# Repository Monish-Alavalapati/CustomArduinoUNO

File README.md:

# CustomArduinoUNO
Made a custom arduino PCB design which is cost effective and has optimized power management
## Overview

This repository contains the necessary files for the custom Arduino board designed using KiCad software. It includes the PCB design, Gerber files, and schematic layout.

## Files Included

1. **PCB Design File**: This file contains the design of the custom Arduino board. It's in KiCad format (.kicad_pcb) and can be opened using KiCad software for further modification.

2. **Gerber Files**: Gerber files are industry-standard files used for PCB manufacturing. These files contain all the necessary information for the fabrication of the PCB. They include layers such as copper traces, solder mask, and silkscreen.

3. **Schematic Layout**: The schematic layout of the custom Arduino board is provided in KiCad format (.sch). It shows the connections and components used in the design.

## How to Use

### Viewing the PCB Design and Schematic Layout

1. Install KiCad: If you haven't already, download and install KiCad from [KiCad's official website](https://www.kicad.org/).

2. Open Files:
   - To view the PCB design, open the `.kicad_pcb` file using KiCad's PCB Layout Editor.
   - To view the schematic layout, open the `.sch` file using KiCad's Schematic Editor.

### Manufacturing the PCB

1. Gerber Files: These are the files you'll need to submit to your PCB manufacturer. Most manufacturers have instructions on their websites for uploading Gerber files.

2. Verify Design: Before sending the files for manufacturing, double-check the design to ensure all connections and components are as intended.

3. Fabrication: Upload the Gerber files to your chosen PCB manufacturer and follow their instructions for fabrication. Make sure to specify any special requirements or preferences.

### Customization

Feel free to modify the design according to your requirements. You can use KiCad to make changes to the PCB layout or schematic as needed. Remember to update the Gerber files if significant changes are made before fabrication.

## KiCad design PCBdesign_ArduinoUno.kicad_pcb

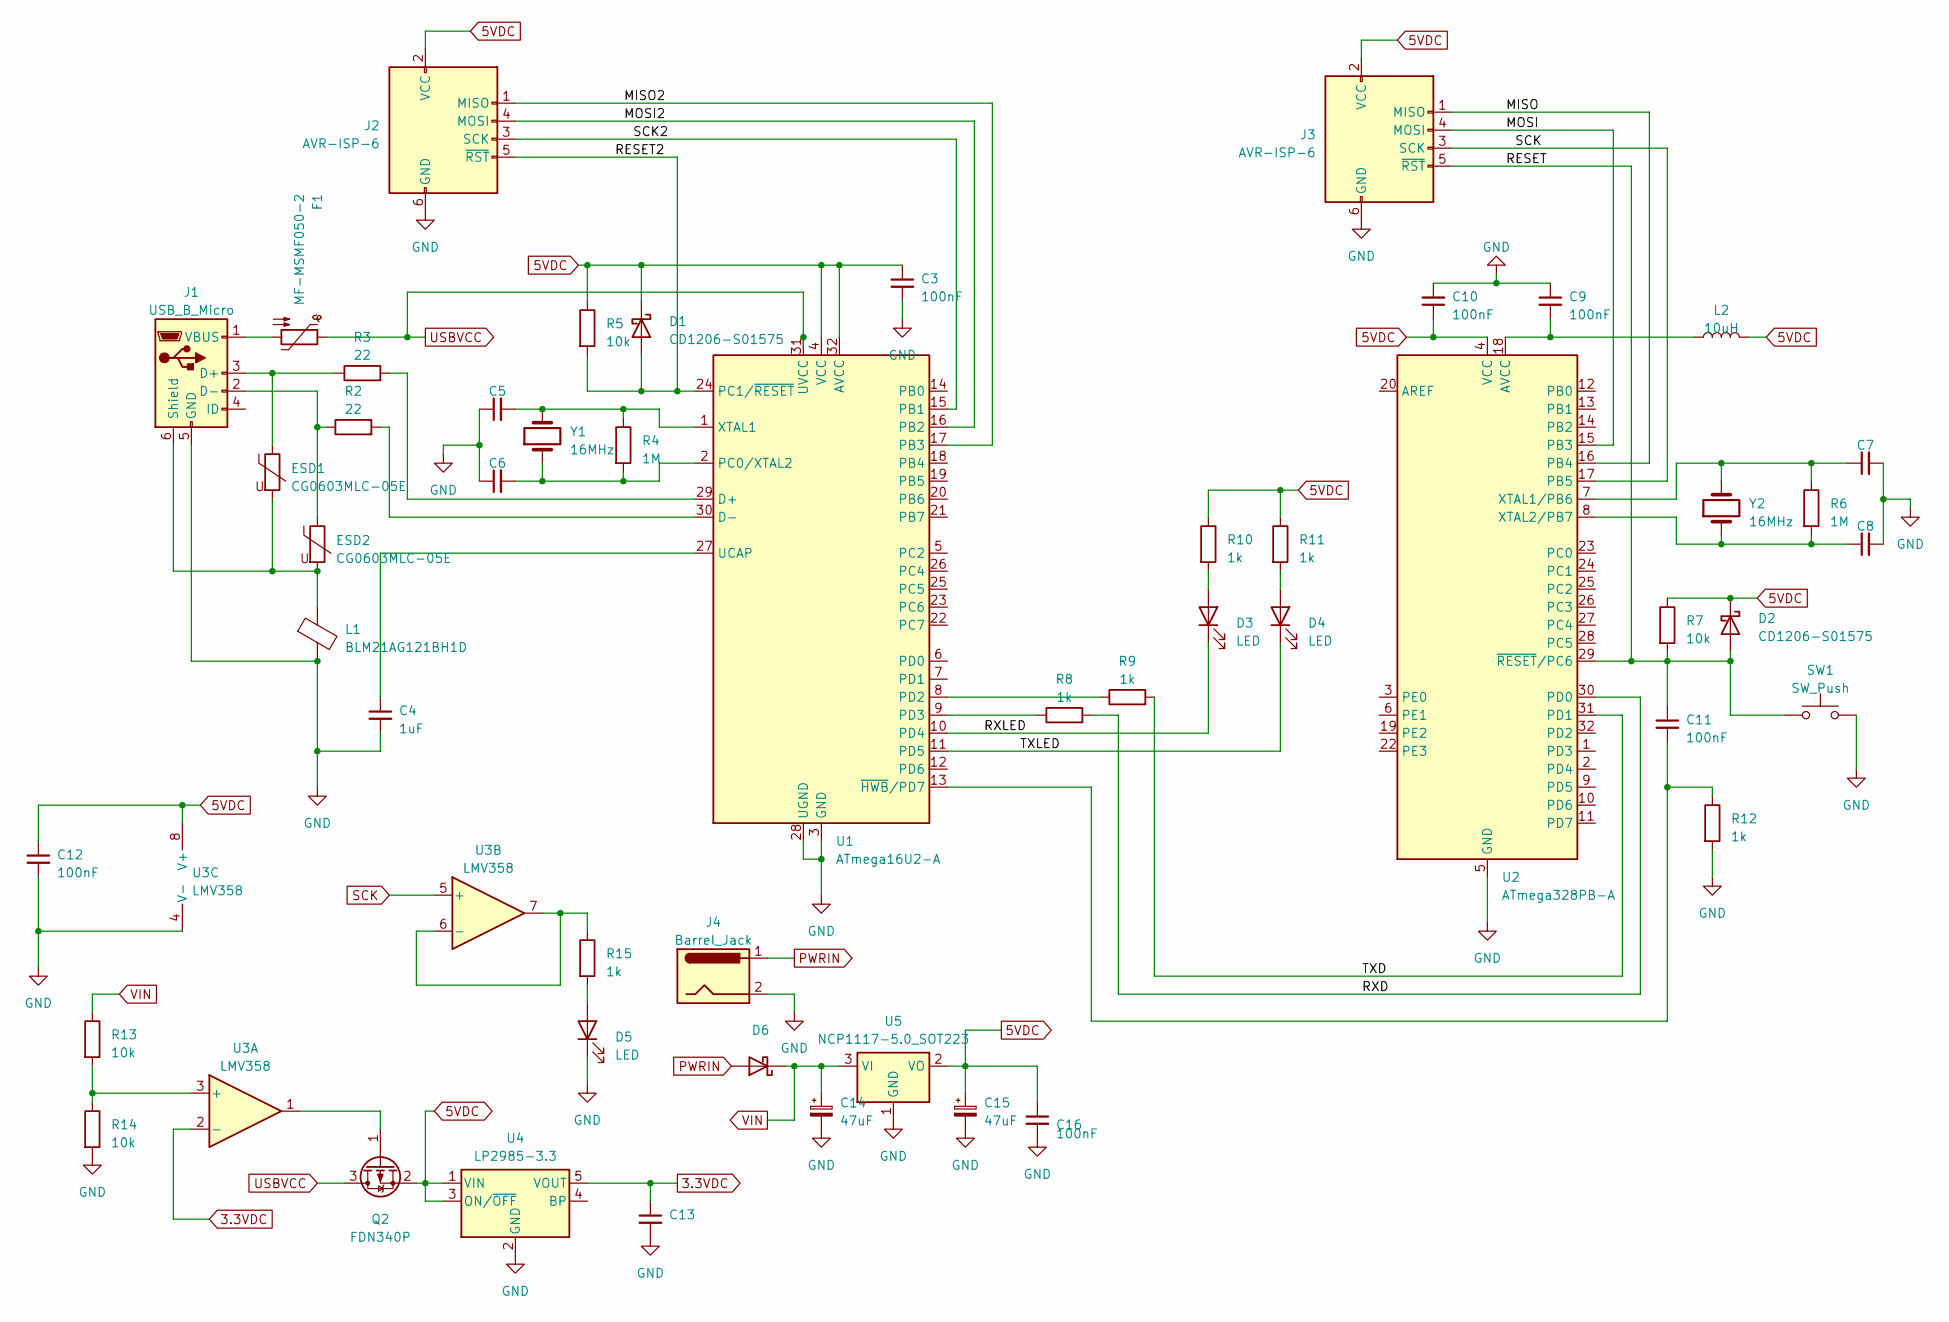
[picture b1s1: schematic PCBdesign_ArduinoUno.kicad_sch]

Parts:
C3, C9, C10, C11, C12, C16: 100nF; C_0603_1608Metric
C4: 1uF; C_0603_1608Metric
C5, C6, C7, C8, C13: C_0603_1608Metric
C14, C15: 47uF; C_Elec_6.3x5.8
D1, D2: CD1206-S01575; D_1206_3216Metric
D3, D4, D5: LED; LED_0603_1608Metric
D6: D_1206_3216Metric
ESD1, ESD2: CG0603MLC-05E; R_0603_1608Metric
F1: MF-MSMF050-2; R_1812_4532Metric
J1: USB_B_Micro; USB_Micro-B_Amphenol_10103594-0001LF_Horizontal
J2, J3: AVR-ISP-6; PinHeader_2x03_P2.54mm_Vertical_SMD
J4: Barrel_Jack; BarrelJack_SwitchcraftConxall_RAPC10U_Horizontal
L1: BLM21AG121BH1D; L_0805_2012Metric
L2: 10uH; L_0603_1608Metric
Q2: FDN340P; SOT-23
R2, R3: 22; R_0603_1608Metric
R4, R6: 1M; R_0603_1608Metric
R5, R7, R13, R14: 10k; R_0603_1608Metric
R8, R9, R10, R11, R12, R15: 1k; R_0603_1608Metric
SW1: SW_Push; SW_Tactile_SPST_NO_Straight_CK_PTS636Sx25SMTRLFS
U1: ATmega16U2-A; TQFP-32_7x7mm_P0.8mm
U2: ATmega328PB-A; TQFP-32_7x7mm_P0.8mm
U3: LMV358; VSSOP-8_3.0x3.0mm_P0.65mm
U4: LP2985-3.3; SOT-23-5
U5: NCP1117-5.0_SOT223; SOT-223-3_TabPin2
Y1, Y2: 16MHz; Crystal_SMD_Abracon_ABM3-2Pin_5.0x3.2mm

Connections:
3.3VDC: C13.1, U3.2 (-), U4.5 (VOUT)
5VDC: C3.1, C10.1, C12.1, C15.1, C16.1, D1.1 (K), D2.1 (K), J2.2 (VCC), J3.2 (VCC), L2.2, Q2.2 (S), R5.1, R7.1, R10.1, R11.1, U1.4 (VCC), U1.32 (AVCC), U2.4 (VCC), U3.8 (V+), U4.1 (VIN), U4.3 (ON/~OFF), U5.2 (VO)
/MISO: J3.1 (MISO), U2.16 (PB4)
/MISO2: J2.1 (MISO), U1.17 (PB3)
/MOSI: J3.4 (MOSI), U2.15 (PB3)
/MOSI2: J2.4 (MOSI), U1.16 (PB2)
/RESET: C11.1, D2.2 (A), J3.5 (~RST), R7.2, SW1.1, U2.29 (~RESET/PC6)
/RESET2: D1.2 (A), J2.5 (~RST), R5.2, U1.24 (PC1/~RESET)
/RXD: R8.2, U2.30 (PD0)
/RXLED: D3.1 (K), U1.10 (PD4)
/SCK2: J2.3 (SCK), U1.15 (PB1)
/TXD: R9.2, U2.31 (PD1)
/TXLED: D4.1 (K), U1.11 (PD5)
GND: C3.2, C4.2, C5.1, C6.1, C7.2, C8.2, C9.1, C10.2, C12.2, C13.2, C14.2, C15.2, C16.2, D5.1 (K), J1.5 (GND), J2.6 (GND), J3.6 (GND), J4.2, L1.2, R12.2, R14.2, SW1.2, U1.3 (GND), U1.28 (UGND), U2.5 (GND), U2.21 (GND), U3.4 (V-), U4.2 (GND), U5.1 (GND)
unnamed: D3.2 (A), R10.2
unnamed: D4.2 (A), R11.2
unnamed: D5.2 (A), R15.2
unnamed: ESD1.1, J1.3 (D+), R3.1
unnamed: ESD2.1, J1.2 (D-), R2.1
unnamed: ESD1.2, ESD2.2, J1.6 (Shield), L1.1
unnamed: F1.2, J1.1 (VBUS)
unnamed: Q2.1 (G), U3.1
unnamed: R3.2, U1.29 (D+)
unnamed: R2.2, U1.30 (D-)
unnamed: C6.2, R4.2, U1.2 (PC0/XTAL2), Y1.1
unnamed: R9.1, U1.8 (PD2)
unnamed: R8.1, U1.9 (PD3)
unnamed: C4.1, U1.27 (UCAP)
unnamed: C5.2, R4.1, U1.1 (XTAL1), Y1.2
unnamed: C11.2, R12.1, U1.13 (~HWB/PD7)
unnamed: C9.2, L2.1, U2.18 (AVCC)
unnamed: C7.1, R6.1, U2.7 (XTAL1/PB6), Y2.2
unnamed: C8.1, R6.2, U2.8 (XTAL2/PB7), Y2.1
unnamed: R13.2, R14.1, U3.3 (+)
unnamed: R15.1, U3.6 (-), U3.7
PWRIN: D6.2 (A), J4.1
SCK: J3.3 (SCK), U2.17 (PB5), U3.5 (+)
USBVCC: F1.1, Q2.3 (D), U1.31 (UVCC)
VIN: C14.1, D6.1 (K), R13.1, U5.3 (VI)

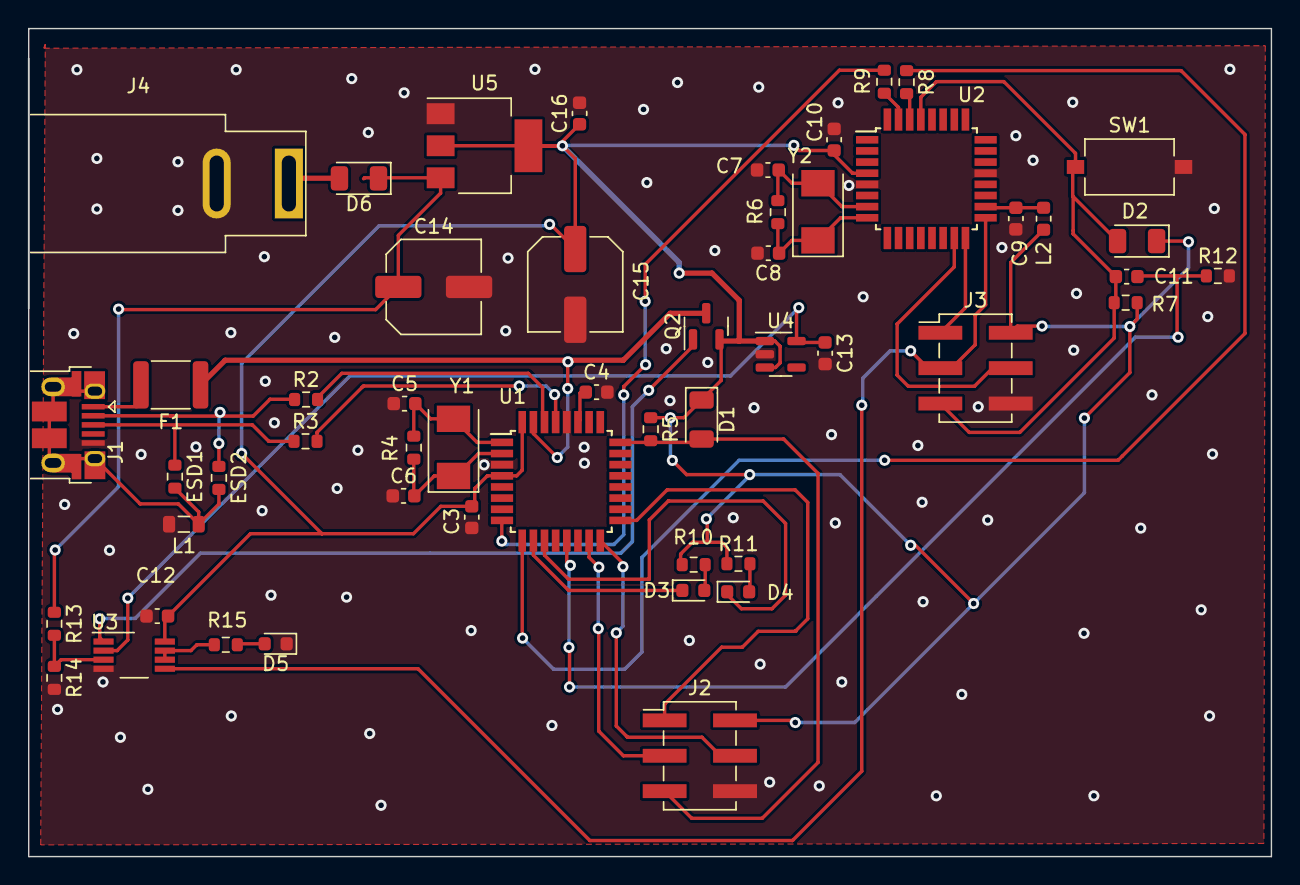
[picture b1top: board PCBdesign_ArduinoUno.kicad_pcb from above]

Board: 2 copper layers, 89.2 x 59.4 mm, 52 parts (0 on the bottom side), 39 nets.
